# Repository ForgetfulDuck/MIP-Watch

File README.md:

# STM32 Fitness Tracker with MIP Display
A simple fitness tracker based on the STM32U0 microcontroller that utilizes low-power modes, DMA-based I2C data transfers, and an ultra-low-power MIP display to maximize battery life.
___
### Hardware Components
| Description | Part |
| :------- | -------:|
| Arm Cortex-M0+ MCU  | [STM32U0](/Datasheets/stm32u031f4.pdf) |
| Accelerometer with built-in pedometer  | [LSM6DSR](/Datasheets/LSM6DSR.pdf) |
| RTC  | [MAX31331](/Datasheets/MAX31331.pdf) |
| MIP display  | [TN0104ANVAANN](/Datasheets/TN0104ANVAANN-GN00_Spec.pdf) |
| Coin Cell  (4.2-3.6V, 120mAh )  | LIR2450 |

### Software + Tools
- PCB Design: KiCAD (Schematic and 4-layer board design)
- Firmware Development: STM32CubeIDE with HAL drivers
- Programming: ST-Link V2 debugger/programmer
- Version Control: Git with structured project management
___
### PCB Design
**4-Layer Stackup: Signal - GND - Power - Signal**:
|  | Image | Contents |
| :-------:  | :-------: | :-------: |
|Schematic| |  |
|Signal| | Short traces, Decoupling caps, Copper pours, Test pads |
|GND| | A continuous ground plane to maximize signal integrity and minimize EMI |
|Power| |  A clean power plane for efficient power distribution with minimal voltage drop |
|DFM | | Designed around JLCPCB's design constraints, with design-for-testability (DFT) considerations, including test points and adequate component spacing. |
___

### System Architecture

```mermaid
---
config:
  theme: base
  themeVariables:
    primaryColor: "#2b3137"
    primaryTextColor: "#fafbfc"
    primaryBorderColor: "#fafbfc"
    lineColor: "#fafbfc"
    secondaryColor: "#24292e"
    tertiaryColor: "#0D1117"
    fontSize: "16px"
    fontFamily: "Segoe UI, Helvetica, Arial, sans-serif"
  nodeSpacing: 30
  rankSpacing: 30
---
flowchart TD
   subgraph SystemArchitecture [ ]
      A[Power On Reset] --> B[MCU Core Initialization<br>HAL, Clock, I2C Bus Clear]
      B --> C[Peripheral Setup<br>GPIO, DMA, I2C,<br>RTC, IMU, Interrupts]
      
      C --> D[Main Control Loop]
      
      D --> E{Job in Queue?}
      E --> F[No] --> G[Enter STOP Mode]
      G --> H[Wait for Sensor Interrupt]
      
      E --> I[Yes] --> J{DMA Available?}
      J --> K[No] --> L[Enter SLEEP Mode]
      L --> M[Wait for DMA Line]
      
      J --> N[Yes] --> O[Start DMA Transfer] --> L
      
      subgraph InterruptSources [Interrupt Handler]
      style InterruptSources fill:#2dba4e,stroke:#ffffff,stroke-width:2px,color:#ffffff
         P[IMU INT1: Step Detection] --> Q[Enqueue Step<br>Job]
         R[IMU INT2: Tap Detection] --> S[Enqueue Tap<br>Job]
         T[RTC INT: Timer Tick] --> U[Enqueue Time<br>Job]
         V[DMA Complete] --> W[Process Sensor Data<br>&<br>Free DMA Resources]
      end
      
      Q --> D
      S --> D
      U --> D
      W --> D
   end
```
___
### Key Features
- **Interrupt-driven firmware:** Interrupts from sensors queue jobs, preventing the need to continuously poll for updated data.
   - The IMU handles step/tap detection and only wakes the MCU when a new event occurs.
   - The RTC generates periodic interrupts for timekeeping and display refreshes.
- **Custom RTC Driver:** Wrote a platform-independent driver for the MAX31331 that provides:
   - Time/date get + set functions
   - Timer configuration + clock calibration
   - Interrupt setup
- **Direct Memory Access (DMA):** I²C data from the sensors is transferred in the background, while the CPU is in SLEEP mode.
- **Dynamic Power Management:** The firmware enters STOP mode when idle and SLEEP mode during DMA operations, waking only to process data from the sensors.
- **Memory-in-Pixel (MIP) display:** The display only consumes energy when the content is updated.

### Build & Flash
- Open project in STM32CubeIDE.
- Build firmware (`Project → Build Project`).
- Connect ST-Link V2 over SWD
   - SWDIO → SWDIO
   - SWCLK → SWCLK
   - VCC   → 3.6-5V
   - GND   → GND
- Flash firmware (`Run -> Run/Debug`)

### Debugging
   - Arm Cortex-M0+ MCUs do not support SWV, so SWO debug output is unavailable.
   - Use CubeIDE debugger with:
      - Breakpoints for interrupt handling.
      - Live Expressions to monitor variables (e.g., step counts, clock).
___
### Roadmap
- **User Input:** Add tactile buttons for UI interaction.
- **Power System:** Integrate a coin-cell holder with a BMS for charging support.
- **Peripheral Control:** Dedicate pins on the MCU to enable/disable sensors for proper power sequencing.
- **UART:** Add UART RX/TX headers for logging & debug.
- **Future Plans:** BLE, heart-rate sensor.

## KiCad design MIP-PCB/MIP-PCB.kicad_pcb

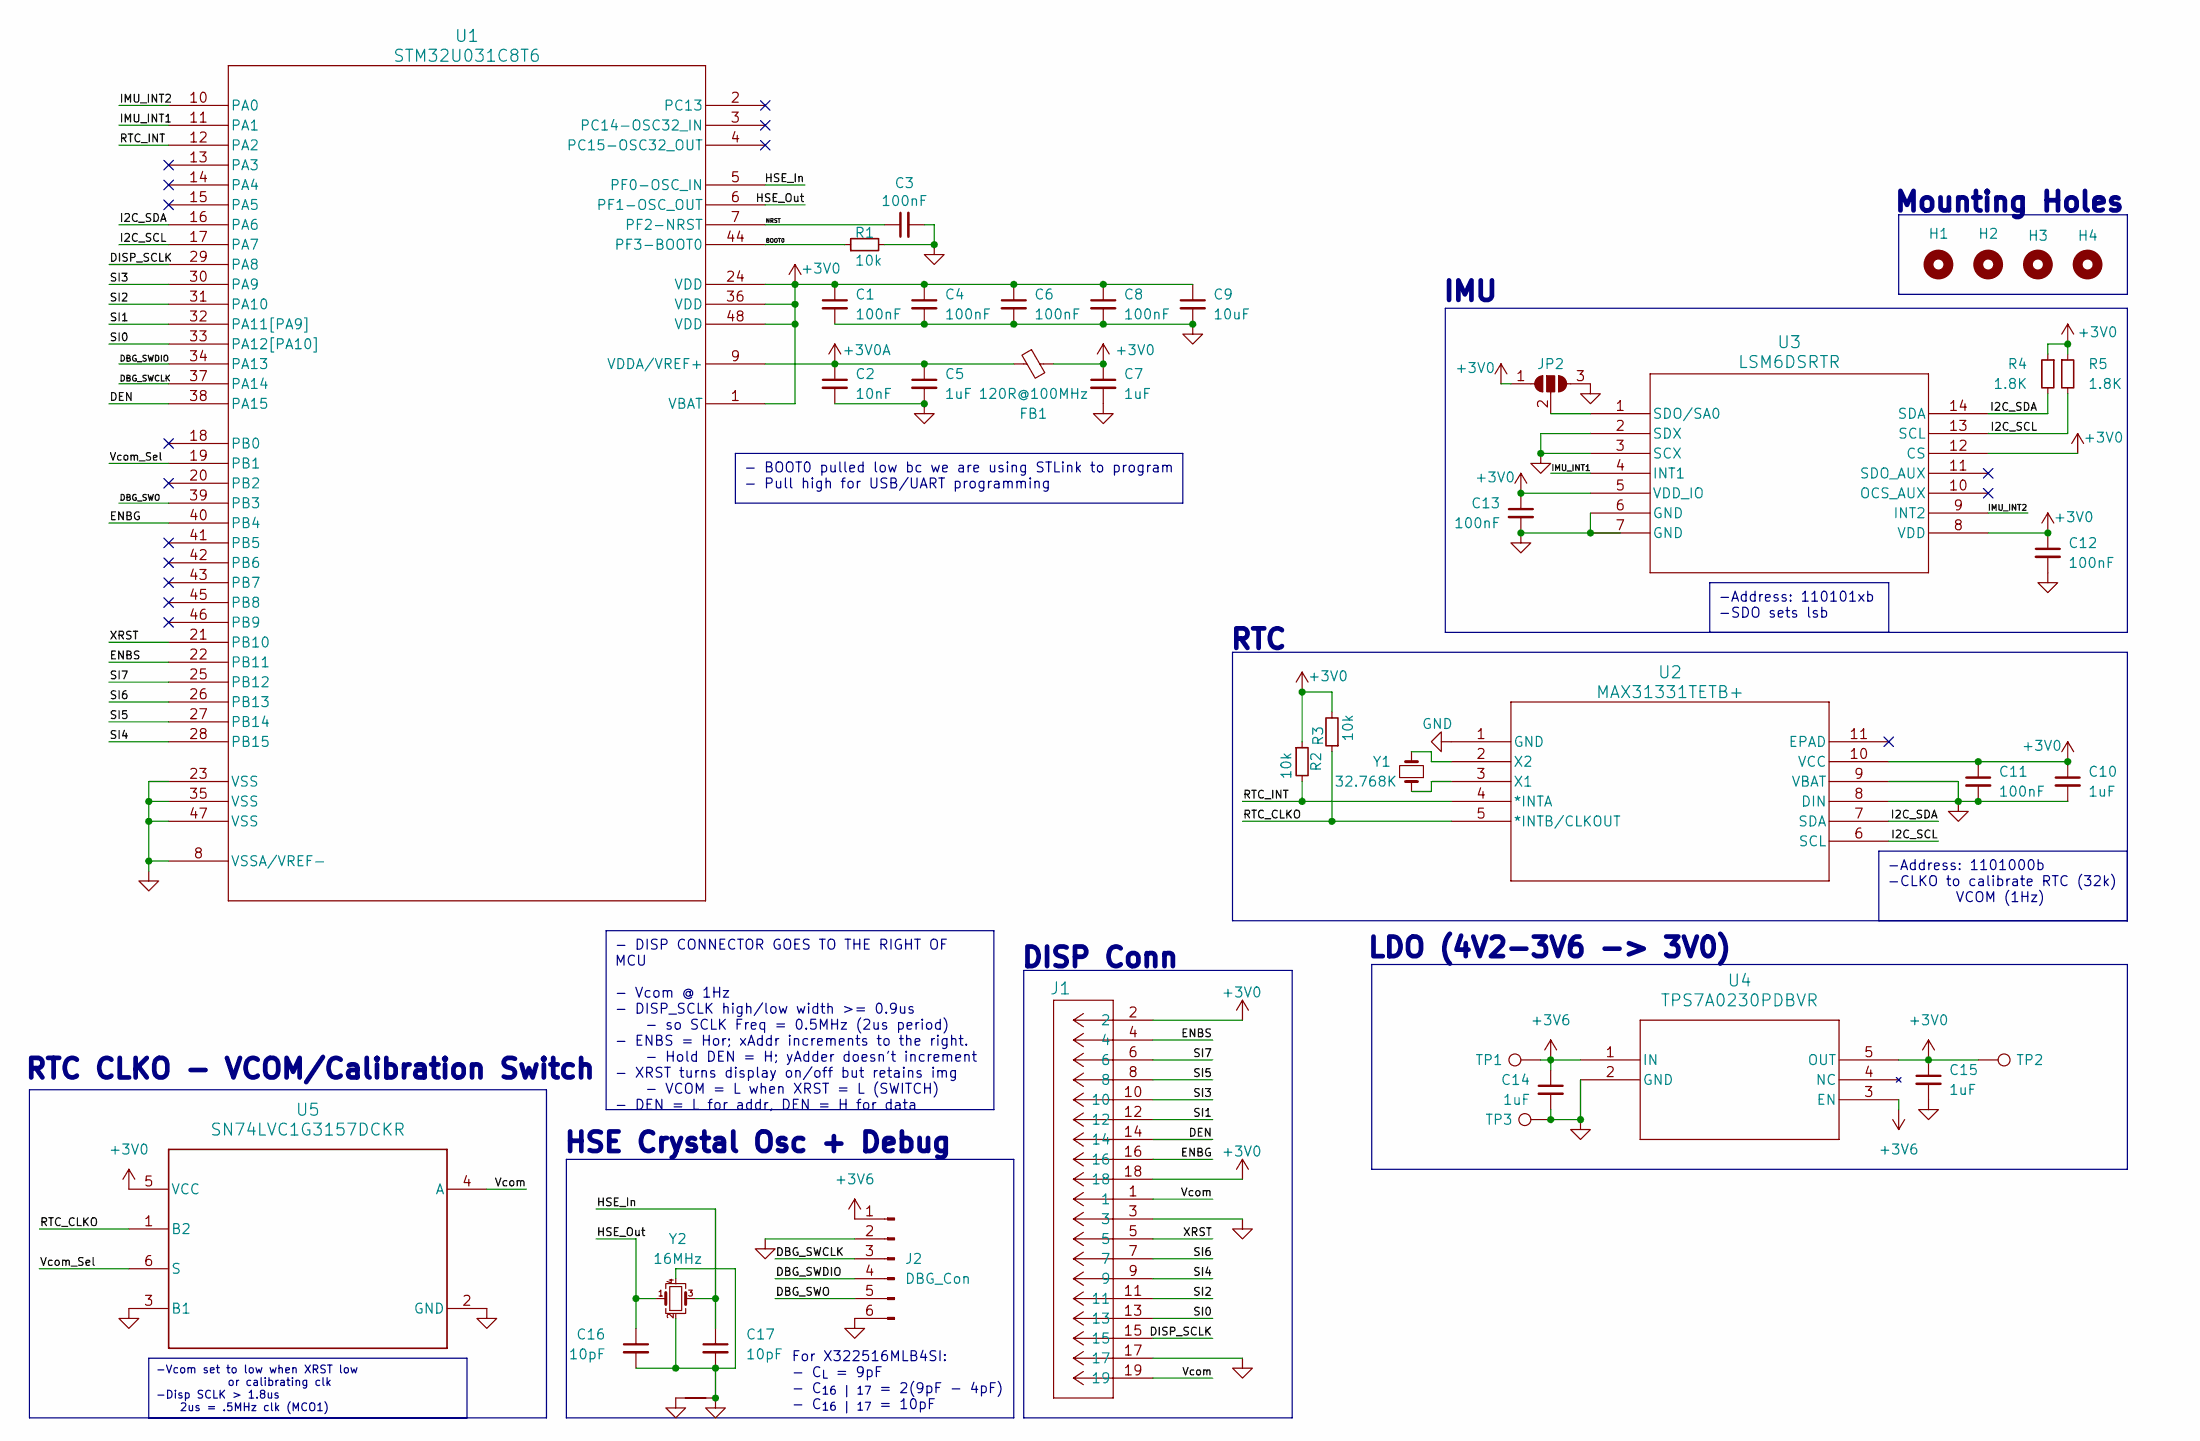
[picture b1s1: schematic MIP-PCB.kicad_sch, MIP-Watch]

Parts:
C1, C3, C4, C6, C8, C11, C12, C13: 100nF; C_0402_1005Metric
C2: 10nF; C_0402_1005Metric
C5, C7, C10, C14, C15: 1uF; C_0402_1005Metric
C9: 10uF; C_0603_1608Metric
C16, C17: 10pF; C_0402_1005Metric
FB1: 120R@100MHz; L_0603_1608Metric
H1, H2, H3, H4: MountingHole; MountingHole_2.2mm_M2
J1: FH35C-19S-0.3SHW99; CONN19_FH35C-19S-0.3SHW99_HIR
J2: DBG_Con; PinHeader_2x03_P2.00mm_Vertical
JP2: SolderJumper_3_Open; SolderJumper-3_P1.3mm_Open_RoundedPad1.0x1.5mm
NT1: NetTie_2
R1, R2, R3: 10k; R_0402_1005Metric
R4, R5: 1.8K; R_0402_1005Metric
TP1, TP2, TP3: TestPoint; TestPoint_Pad_D1.0mm
U1: STM32U031C8T6; LQFP48_STM-L
U2: MAX31331TETB+; 21-0137_T1033-1C_MXM
U3: LSM6DSRTR; LGA-14L_2P5X3X0P83_STM-L
U4: TPS7A0230PDBVR; SOT23_DBV_TEX
U5: SN74LVC1G3157DCKR; DCK0006A_N
Y1: 32.768K; Crystal_SMD_3215-2Pin_3.2x1.5mm
Y2: 16MHz; Crystal_SMD_3225-4Pin_3.2x2.5mm

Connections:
+3V0: C1.1, C4.1, C6.1, C7.1, C8.1, C9.1, C10.1, C11.1, C12.1, C13.1, C15.1, FB1.2, J1.2, J1.18, JP2.1 (A), R2.1, R3.2, R4.1, R5.1, TP2.1, U1.1 (VBAT), U1.24 (VDD), U1.36 (VDD), U1.48 (VDD), U2.10 (VCC), U3.5 (VDD_IO), U3.8 (VDD), U3.12 (CS), U4.5 (OUT), U5.5 (VCC)
+3V0A: C2.1, C5.1, FB1.1, U1.9 (VDDA/VREF+)
+3V6: C14.1, J2.1, TP1.1, U4.1 (IN), U4.3 (EN)
/BOOT0: R1.1, U1.44 (PF3-BOOT0)
/DBG_SWCLK: J2.3, U1.37 (PA14)
/DBG_SWDIO: J2.4, U1.34 (PA13)
/DBG_SWO: J2.5, U1.39 (PB3)
/DEN: J1.14, U1.38 (PA15)
/DISP_SCLK: J1.15, U1.29 (PA8)
/ENBG: J1.16, U1.40 (PB4)
/ENBS: J1.4, U1.22 (PB11)
/HSE_In: C17.1, U1.5 (PF0-OSC_IN), Y2.3
/HSE_Out: C16.1, U1.6 (PF1-OSC_OUT), Y2.1
/I2C_SCL: R5.2, U1.17 (PA7), U2.6 (SCL), U3.13 (SCL)
/I2C_SDA: R4.2, U1.16 (PA6), U2.7 (SDA), U3.14 (SDA)
/IMU_INT1: U1.11 (PA1), U3.4 (INT1)
/IMU_INT2: U1.10 (PA0), U3.9 (INT2)
/NRST: C3.1, U1.7 (PF2-NRST)
/RTC_CLKO: R3.1, U2.5 (*INTB/CLKOUT), U5.1 (B2)
/RTC_INT: R2.2, U1.12 (PA2), U2.4 (*INTA)
/SI0: J1.13, U1.33 (PA12[PA10])
/SI1: J1.12, U1.32 (PA11[PA9])
/SI2: J1.11, U1.31 (PA10)
/SI3: J1.10, U1.30 (PA9)
/SI4: J1.9, U1.28 (PB15)
/SI5: J1.8, U1.27 (PB14)
/SI6: J1.7, U1.26 (PB13)
/SI7: J1.6, U1.25 (PB12)
/Vcom: J1.1, J1.19, U5.4 (A)
/Vcom_Sel: U1.19 (PB1), U5.6 (S)
/XRST: J1.5, U1.21 (PB10)
GND: C1.2, C2.2, C3.2, C4.2, C5.2, C6.2, C7.2, C8.2, C9.2, C10.2, C11.2, C12.2, C13.2, C14.2, C15.2, J1.3, J1.17, J2.2, J2.6, JP2.3 (B), NT1.1, R1.2, TP3.1, U1.8 (VSSA/VREF-), U1.23 (VSS), U1.35 (VSS), U1.47 (VSS), U2.1 (GND), U2.8 (DIN), U2.9 (VBAT), U3.2 (SDX), U3.3 (SCX), U3.6 (GND), U3.7 (GND), U4.2 (GND), U5.2 (GND), U5.3 (B1)
GND_HSE: C16.2, C17.2, NT1.2, Y2.2, Y2.4
unnamed: JP2.2 (C), U3.1 (SDO/SA0)
unnamed: U2.3 (X1), Y1.1
unnamed: U2.2 (X2), Y1.2

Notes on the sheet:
-Address: 1101000b -CLKO to calibrate RTC (32k) VCOM (1Hz)
-Address: 110101xb -SDO sets lsb
- BOOT0 pulled low bc we are using STLink to program - Pull high for USB/UART programming
- DISP CONNECTOR GOES TO THE RIGHT OF MCU - Vcom @ 1Hz - DISP_SCLK high/low width >= 0.9us - so SCLK Freq = 0.5MHz (2us period) - ENBS = Hor; xAddr increments to the right. - Hold DEN = H; yAdder doesn't increment - XRST turns display on/off but retains img - VCOM = L when XRST = L (SWITCH) - DEN =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
-Vcom set to low when XRST low or calibrating clk -Disp SCLK > 1.8us 2us = .5MHz clk (MCO1)
RTC
LDO (4V2-3V6 -> 3V0)
For X322516MLB4SI: - C_{L} = 9pF - C_{16 | 17} = 2(9pF - 4pF) - C_{16 | 17} = 10pF
Mounting Holes
HSE Crystal Osc + Debug
RTC CLKO - VCOM/Calibration Switch
IMU
DISP Conn

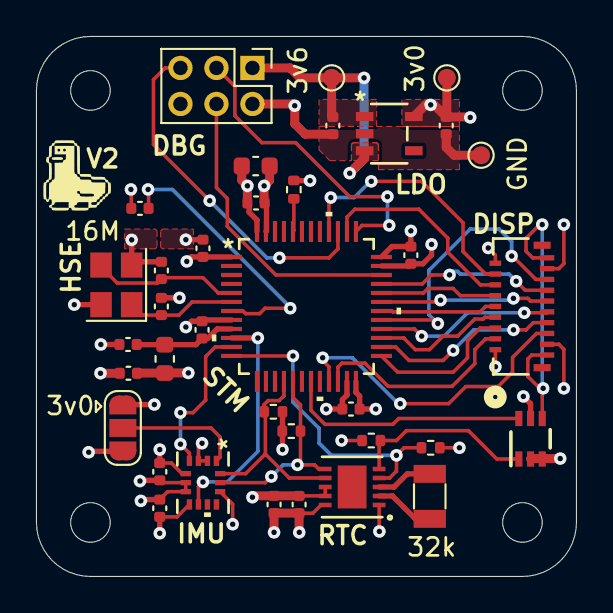
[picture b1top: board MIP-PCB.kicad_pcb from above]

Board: 4 copper layers, 30.0 x 30.0 mm, 40 parts (0 on the bottom side), 36 nets.

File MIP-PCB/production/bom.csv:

Designator,Footprint,Quantity,Value,LCSC Part #
"C1, C11, C12, C13, C3, C4, C6, C8",0402,8,100nF,
"C10, C14, C15, C5, C7",0402,5,1uF,
"C16, C17",0402,2,10pF,
C2,0402,1,10nF,
C9,0603,1,10uF,
FB1,0603,1,120R@100MHz,
J1,CONN19_FH35C-19S-0.3SHW99_HIR,1,FH35C-19S-0.3SHW99,
J2,PinHeader_2x03_P2.00mm_Vertical,1,DBG_Con,
"R1, R2, R3",0402,3,10k,
"R4, R5",0402,2,1.8K,
"TP1, TP2, TP3",TestPoint_Pad_D1.0mm,3,TestPoint,
U1,LQFP48_STM-L,1,STM32U031C8T6,
U2,21-0137_T1033-1C_MXM,1,MAX31331TETB+,
U3,LGA-14L_2P5X3X0P83_STM-L,1,LSM6DSRTR,
U4,SOT23_DBV_TEX,1,TPS7A0230PDBVR,
U5,DCK0006A_N,1,SN74LVC1G3157DCKR,
Y1,Crystal_SMD_3215-2Pin_3.2x1.5mm,1,32.768K,
Y2,Crystal_SMD_3225-4Pin_3.2x2.5mm,1,16MHz,

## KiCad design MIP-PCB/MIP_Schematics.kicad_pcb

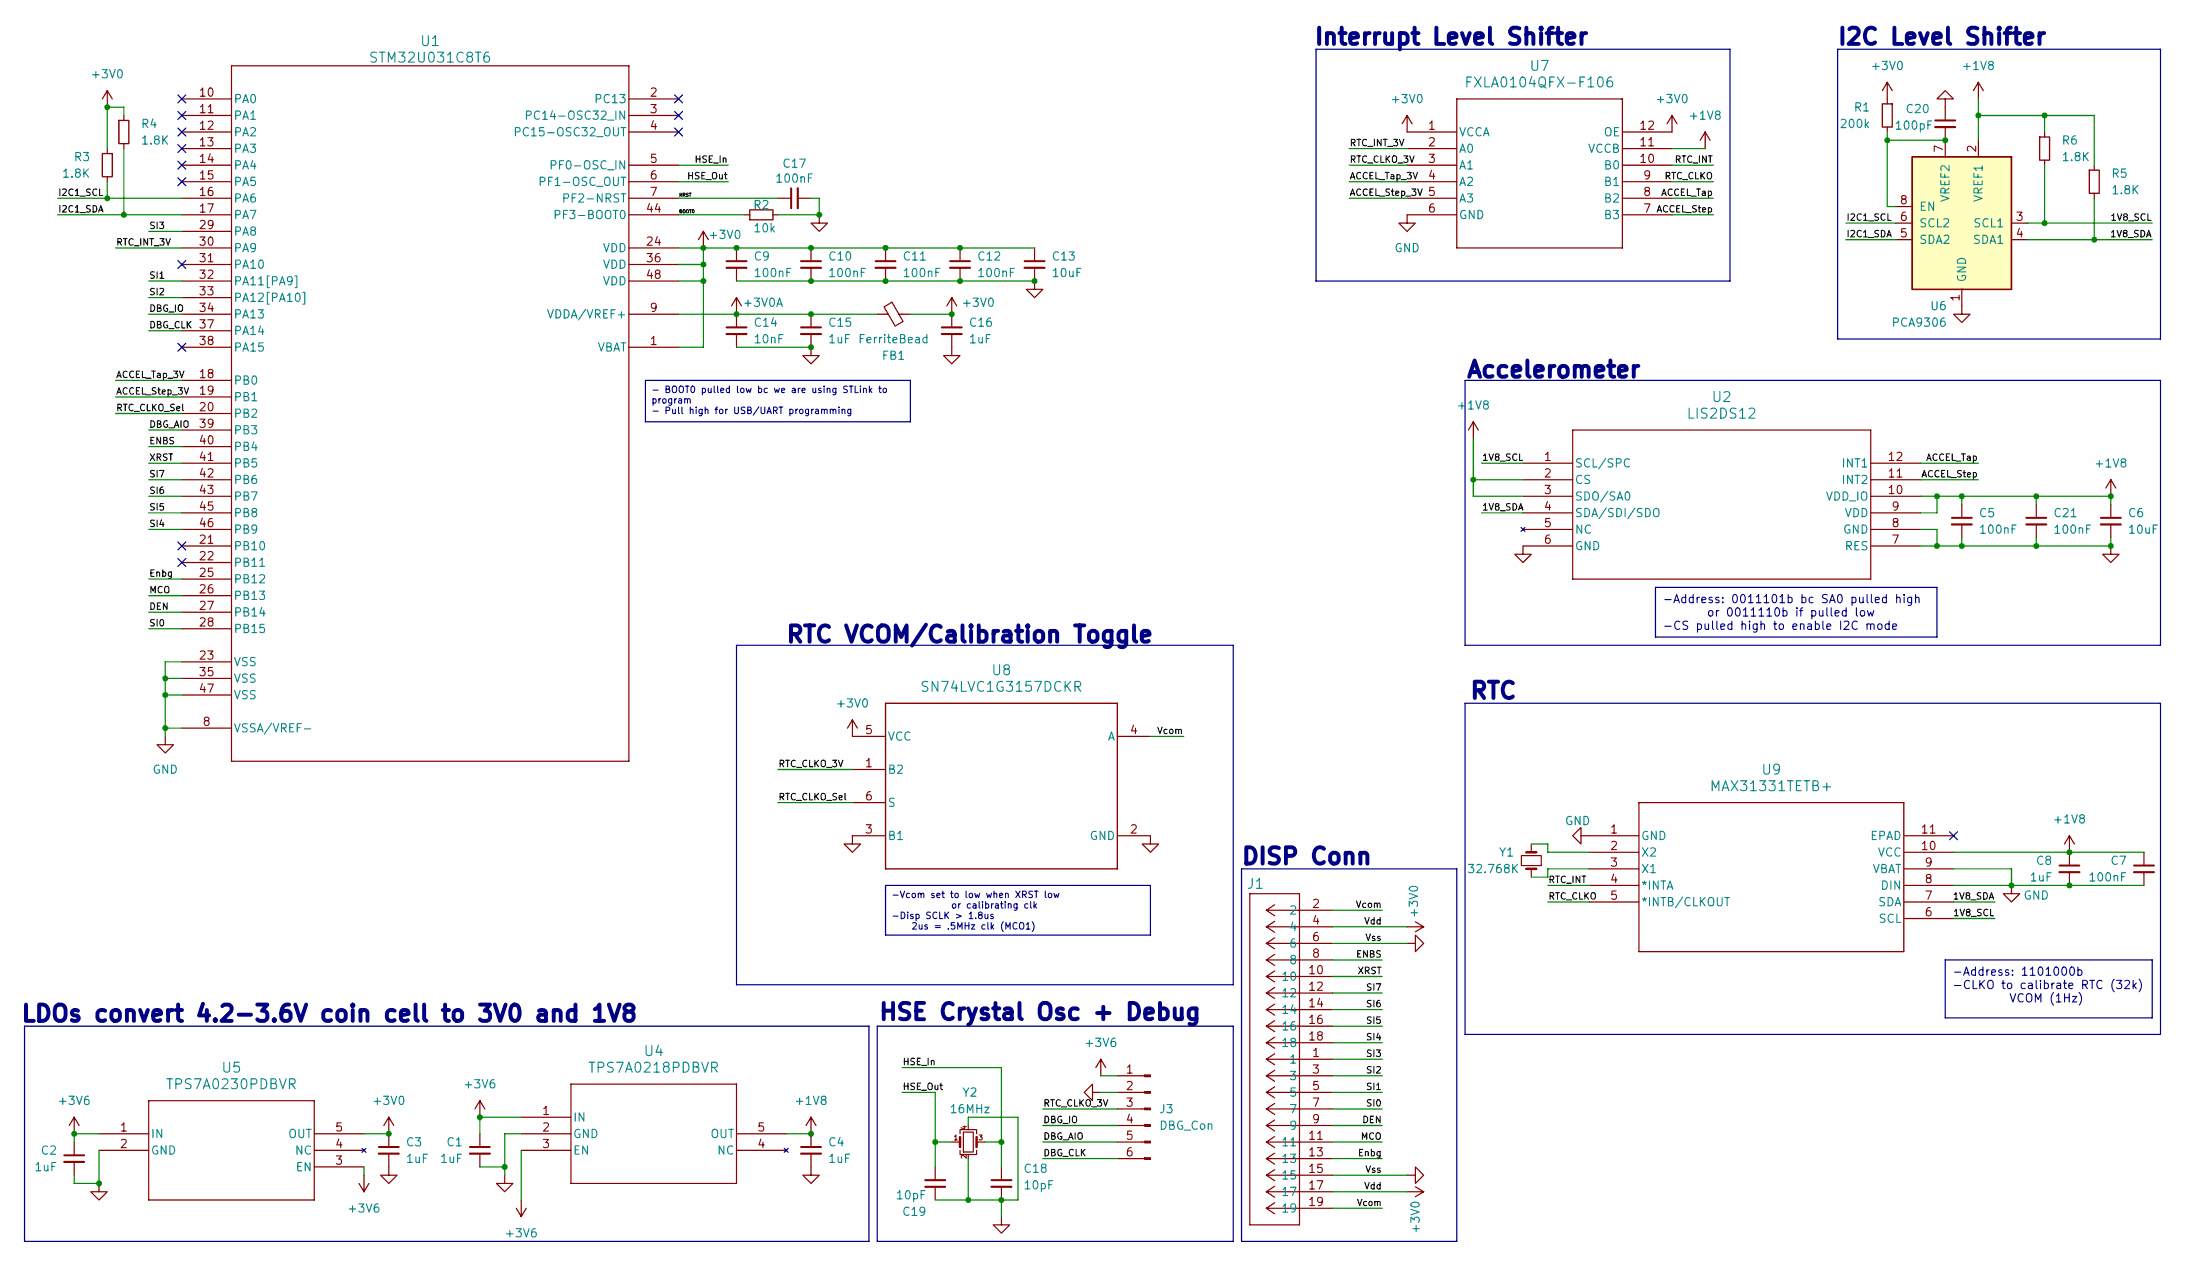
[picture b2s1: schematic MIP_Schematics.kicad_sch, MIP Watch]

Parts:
C1, C2, C3, C4, C8, C15, C16: 1uF; C_0402_1005Metric
C5, C7, C9, C10, C11, C12, C17, C21: 100nF; C_0402_1005Metric
C6, C13: 10uF; C_0603_1608Metric
C14: 10nF; C_0402_1005Metric
C18, C19: 10pF; C_0402_1005Metric
C20: 100pF; C_0402_1005Metric
FB1: FerriteBead; L_0603_1608Metric
J1: FH35C-19S-0.3SHW99; CONN19_FH35C-19S-0.3SHW99_HIR
J3: DBG_Con; PinHeader_2x03_P2.00mm_Vertical
R1: 200k; R_0402_1005Metric
R2: 10k; R_0402_1005Metric
R3, R4, R5, R6: 1.8K; R_0402_1005Metric
U1: STM32U031C8T6; LQFP48_STM
U2: LIS2DS12; LGA-12_2X2X0P86_STM
U4: TPS7A0218PDBVR; SOT_233DBVR_TEX
U5: TPS7A0230PDBVR; SOT23_DBV_TEX
U6: PCA9306; SSOP-8_2.95x2.8mm_P0.65mm
U7: FXLA0104QFX-F106; UMLP12_1P7X2_ONS
U8: SN74LVC1G3157DCKR; DCK0006A_N
U9: MAX31331TETB+; 21-0137_T1033-1C_MXM
Y1: 32.768K; Crystal_SMD_2012-2Pin_2.0x1.2mm
Y2: 16MHz; Crystal_SMD_3225-4Pin_3.2x2.5mm

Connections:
+1V8: C4.1, C5.1, C6.1, C7.1, C8.1, C21.1, R5.1, R6.1, U2.2 (CS), U2.3 (SDO/SA0), U2.9 (VDD), U2.10 (VDD_IO), U4.5 (OUT), U6.2 (VREF1), U7.11 (VCCB), U9.10 (VCC)
+3V0: C3.1, C9.1, C10.1, C11.1, C12.1, C13.1, C16.1, FB1.2, J1.4, J1.17, R1.1, R3.1, R4.1, U1.1 (VBAT), U1.24 (VDD), U1.36 (VDD), U1.48 (VDD), U5.5 (OUT), U7.1 (VCCA), U7.12 (OE), U8.5 (VCC)
+3V0A: C14.1, C15.1, FB1.1, U1.9 (VDDA/VREF+)
+3V6: C1.1, C2.1, J3.1, U4.1 (IN), U4.3 (EN), U5.1 (IN), U5.3 (EN)
/1V8_SCL: R6.2, U2.1 (SCL/SPC), U6.3 (SCL1), U9.6 (SCL)
/1V8_SDA: R5.2, U2.4 (SDA/SDI/SDO), U6.4 (SDA1), U9.7 (SDA)
/ACCEL_Step: U2.11 (INT2), U7.7 (B3)
/ACCEL_Step_3V: U1.19 (PB1), U7.5 (A3)
/ACCEL_Tap: U2.12 (INT1), U7.8 (B2)
/ACCEL_Tap_3V: U1.18 (PB0), U7.4 (A2)
/BOOT0: R2.1, U1.44 (PF3-BOOT0)
/DBG_AIO: J3.5, U1.39 (PB3)
/DBG_CLK: J3.6, U1.37 (PA14)
/DBG_IO: J3.4, U1.34 (PA13)
/DEN: J1.9, U1.27 (PB14)
/ENBS: J1.8, U1.40 (PB4)
/Enbg: J1.13, U1.25 (PB12)
/HSE_In: C18.1, U1.5 (PF0-OSC_IN), Y2.3
/HSE_Out: C19.2, U1.6 (PF1-OSC_OUT), Y2.1
/I2C1_SCL: R3.2, U1.16 (PA6), U6.6 (SCL2)
/I2C1_SDA: R4.2, U1.17 (PA7), U6.5 (SDA2)
/MCO: J1.11, U1.26 (PB13)
/NRST: C17.1, U1.7 (PF2-NRST)
/RTC_CLKO: U7.9 (B1), U9.5 (*INTB/CLKOUT)
/RTC_CLKO_3V: J3.3, U7.3 (A1), U8.1 (B2)
/RTC_CLKO_Sel: U1.20 (PB2), U8.6 (S)
/RTC_INT: U7.10 (B0), U9.4 (*INTA)
/RTC_INT_3V: U1.30 (PA9), U7.2 (A0)
/SI0: J1.7, U1.28 (PB15)
/SI1: J1.5, U1.32 (PA11[PA9])
/SI2: J1.3, U1.33 (PA12[PA10])
/SI3: J1.1, U1.29 (PA8)
/SI4: J1.18, U1.46 (PB9)
/SI5: J1.16, U1.45 (PB8)
/SI6: J1.14, U1.43 (PB7)
/SI7: J1.12, U1.42 (PB6)
/Vcom: J1.2, J1.19, U8.4 (A)
/XRST: J1.10, U1.41 (PB5)
GND: C1.2, C2.2, C3.2, C4.2, C5.2, C6.2, C7.2, C8.2, C9.2, C10.2, C11.2, C12.2, C13.2, C14.2, C15.2, C16.2, C17.2, C18.2, C19.1, C20.1, C21.2, J1.6, J1.15, J3.2, R2.2, U1.8 (VSSA/VREF-), U1.23 (VSS), U1.35 (VSS), U1.47 (VSS), U2.6 (GND), U2.7 (RES), U2.8 (GND), U4.2 (GND), U5.2 (GND), U6.1 (GND), U7.6 (GND), U8.2 (GND), U8.3 (B1), U9.1 (GND), U9.8 (DIN), U9.9 (VBAT), Y2.2, Y2.4
unnamed: C20.2, R1.2, U6.7 (VREF2), U6.8 (EN)
unnamed: U9.3 (X1), Y1.1
unnamed: U9.2 (X2), Y1.2

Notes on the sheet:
-Vcom set to low when XRST low or calibrating clk -Disp SCLK > 1.8us 2us = .5MHz clk (MCO1)
-Address: 1101000b -CLKO to calibrate RTC (32k) VCOM (1Hz)
-Address: 0011101b bc SA0 pulled high or 0011110b if pulled low -CS pulled high to enable I2C mode
- BOOT0 pulled low bc we are using STLink to program - Pull high for USB/UART programming
LDOs convert 4.2-3.6V coin cell to 3V0 and 1V8
HSE Crystal Osc + Debug
I2C Level Shifter
RTC
Interrupt Level Shifter
RTC VCOM/Calibration Toggle
DISP Conn
Accelerometer

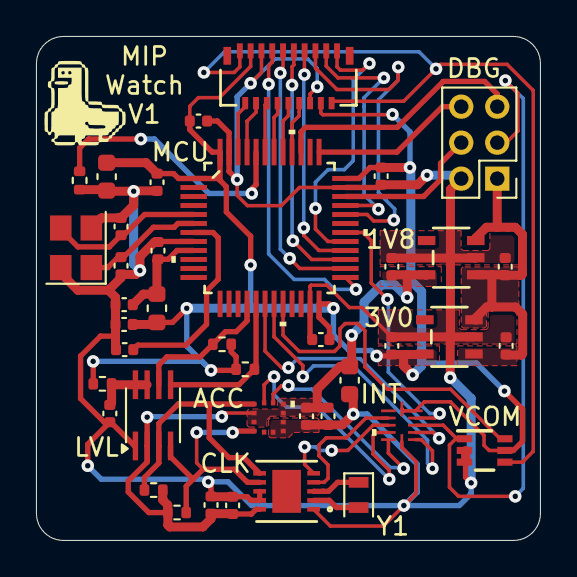
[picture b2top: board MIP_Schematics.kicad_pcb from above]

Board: 2 copper layers, 28.0 x 28.0 mm, 40 parts (0 on the bottom side), 42 nets.

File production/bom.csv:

Designator,Footprint,Quantity,Value,LCSC Part #
"C1, C15, C16, C2, C3, C4, C8",0402,7,1uF,
"C10, C11, C12, C17, C21, C5, C7, C9",0402,8,100nF,
"C13, C6",0603,2,10uF,
C14,0402,1,10nF,
"C18, C19",0402,2,10pF,
C20,0402,1,100pF,
FB1,0603,1,FerriteBead,
J1,CONN19_FH35C-19S-0.3SHW99_HIR,1,FH35C-19S-0.3SHW99,
J3,PinHeader_2x03_P2.00mm_Vertical,1,DBG_Con,
R1,0402,1,200k,
R2,0402,1,10k,
"R3, R4, R5, R6",0402,4,1.8K,
U1,LQFP48_STM,1,STM32U031C8T6,
U2,LGA-12_2X2X0P86_STM,1,LIS2DS12,
U4,SOT_233DBVR_TEX,1,TPS7A0218PDBVR,
U5,SOT23_DBV_TEX,1,TPS7A0230PDBVR,
U6,SSOP-8_2.95x2.8mm_P0.65mm,1,PCA9306,
U7,UMLP12_1P7X2_ONS,1,FXLA0104QFX-F106,
U8,DCK0006A_N,1,SN74LVC1G3157DCKR,
U9,21-0137_T1033-1C_MXM,1,MAX31331TETB+,
Y1,Crystal_SMD_2012-2Pin_2.0x1.2mm,1,128k,
Y2,Crystal_SMD_3225-4Pin_3.2x2.5mm,1,16MHz,

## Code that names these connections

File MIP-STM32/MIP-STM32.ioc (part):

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Mcu.Name=STM32U031C8Tx
Mcu.Package=LQFP48
Mcu.UserName=STM32U031C8Tx
PA0.GPIOParameters=GPIO_Label
PA0.GPIO_Label=IMU_INT2
PA0.Signal=GPXTI0
PA1.GPIOParameters=GPIO_PuPd,GPIO_Label
PA1.GPIO_Label=IMU_INT1_Float
PA1.GPIO_PuPd=GPIO_PULLDOWN
PA1.Signal=GPIO_Input
PA10.GPIOParameters=GPIO_Label
PA10.GPIO_Label=SI2
PA10.Signal=GPIO_Output
PA11\ [PA9].GPIOParameters=GPIO_Label
PA11\ [PA9].GPIO_Label=SI1
PA11\ [PA9].Signal=GPIO_Output
PA12\ [PA10].GPIOParameters=GPIO_Label
PA12\ [PA10].GPIO_Label=SI0
PA12\ [PA10].Signal=GPIO_Output
PA13\ (SWDIO).GPIOParameters=GPIO_Label
PA13\ (SWDIO).GPIO_Label=DBG_SWDIO
PA13\ (SWDIO).Mode=Serial_Wire
PA13\ (SWDIO).Signal=DEBUG_JTMS-SWDIO
PA14\ (SWCLK).GPIOParameters=GPIO_Label
PA14\ (SWCLK).GPIO_Label=DBG_SWCLK
PA14\ (SWCLK).Mode=Serial_Wire
PA14\ (SWCLK).Signal=DEBUG_JTCK-SWCLK
PA15.GPIOParameters=GPIO_Label
PA15.GPIO_Label=DEN
PA15.Signal=GPIO_Output
PA2.GPIOParameters=GPIO_Label,GPIO_ModeDefaultEXTI
PA2.GPIO_Label=RTC_INT
PA2.GPIO_ModeDefaultEXTI=GPIO_MODE_IT_FALLING
PA2.Signal=GPXTI2
PA3.Signal=GPIO_Analog
PA4.Signal=GPIO_Analog
PA5.Signal=GPIO_Analog
PA6.Mode=I2C
PA6.Signal=I2C3_SDA
PA7.Mode=I2C
PA7.Signal=I2C3_SCL
PA8.GPIOParameters=GPIO_Label
PA8.GPIO_Label=DISP_SCLK
PA8.Signal=GPIO_Analog
PA9.GPIOParameters=GPIO_Label
PA9.GPIO_Label=SI3
PA9.Signal=GPIO_Output
PB0.Signal=GPIO_Analog
PB1.GPIOParameters=GPIO_Label
PB1.GPIO_Label=Vcom_Sel
PB1.Signal=GPIO_Output
PB10.GPIOParameters=GPIO_Label
PB10.GPIO_Label=XRST
PB10.Signal=GPIO_Output
PB11.GPIOParameters=GPIO_Label
PB11.GPIO_Label=ENBS
PB11.Signal=GPIO_Output
PB12.GPIOParameters=GPIO_Label
PB12.GPIO_Label=SI7
PB12.Signal=GPIO_Output
PB13.GPIOParameters=GPIO_Label
PB13.GPIO_Label=SI6
PB13.Signal=GPIO_Output
PB14.GPIOParameters=GPIO_Label
PB14.GPIO_Label=SI5
PB14.Signal=GPIO_Output
PB15.GPIOParameters=GPIO_Label
PB15.GPIO_Label=SI4
PB15.Signal=GPIO_Output
PB2.Signal=GPIO_Analog
PB3.Signal=GPIO_Analog
PB4.GPIOParameters=GPIO_Label
PB4.GPIO_Label=ENBG
PB4.Signal=GPIO_Output
PB5.Signal=GPIO_Analog
PB6.Signal=GPIO_Analog
PB7.Signal=GPIO_Analog
PB8.Signal=GPIO_Analog
PB9.Signal=GPIO_Analog
PC13.Signal=GPIO_Analog
PC14-OSC32_IN.Signal=GPIO_Analog
PC15-OSC32_OUT.Signal=GPIO_Analog
PF0-OSC_IN.Signal=RCC_OSC_IN
PF1-OSC_OUT.Signal=RCC_OSC_OUT
RCC.HSE_VALUE=16000000
RCC.SYSCLKFreq_VALUE=16000000
board=custom

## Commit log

2025-08-06 Added KiCad files
2025-08-06 Added readme
2025-08-06 Added image labels
2025-08-28 V2 of the MIP Watch - Updated PCB - Added test points - Uses single LDO for power regulation - Changed IMU to LSM6DSR - Added STM32 Code. - Functional prototype with interrupt based peripheral reads.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
2025-08-29 MIP Watch V2: Added STM32 project files. - Updated README.md - Disabled IMU_INT1 to avoid I3C conflict.
2025-08-29 Enabled Stop/Sleep modes! Fixed typos in README.md
2025-08-29 Enabled STOP/SLEEP modes! Fixed typos in README
2025-09-06 Added Low-Power Run Mode (1MHz Clock) Disabled MCO2 to save power Configured unsused pins as analog
